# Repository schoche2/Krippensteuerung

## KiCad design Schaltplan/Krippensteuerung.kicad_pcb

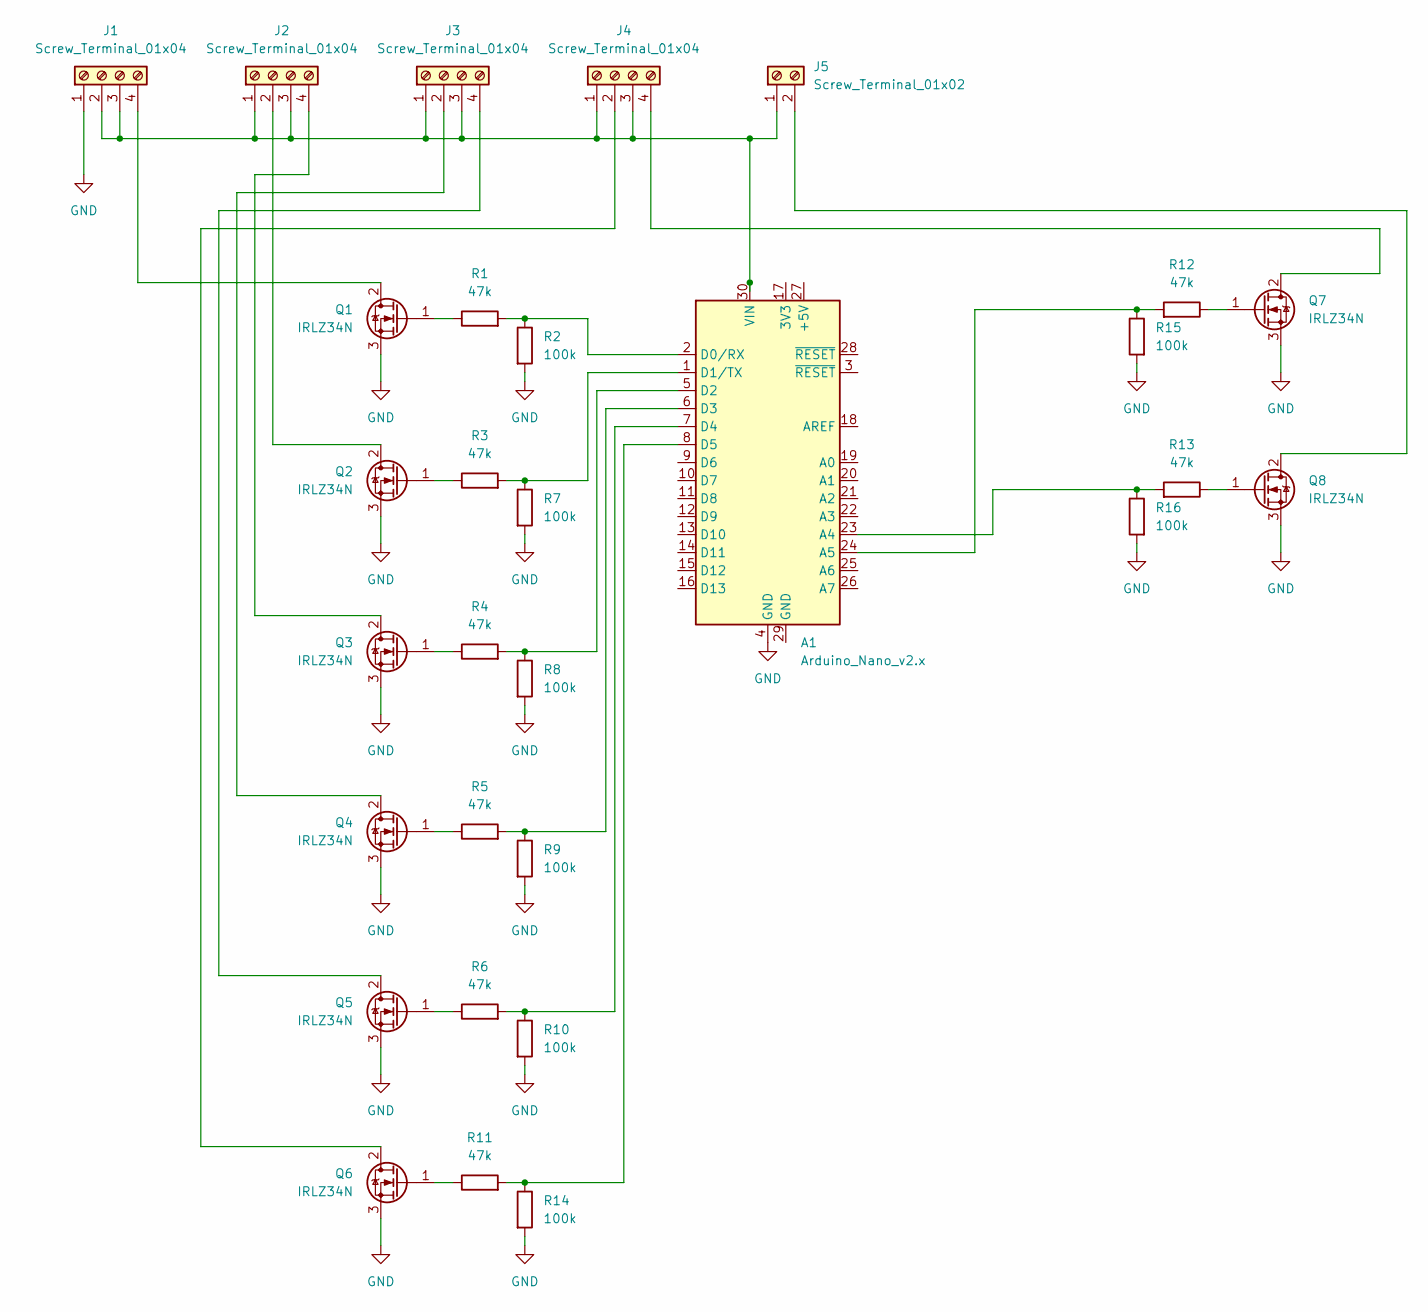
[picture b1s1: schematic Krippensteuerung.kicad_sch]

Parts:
A1: Arduino_Nano_v2.x; Arduino_Nano
J1, J2, J3, J4: Screw_Terminal_01x04; TerminalBlock_Altech_AK300-4_P5.00mm
J5: Screw_Terminal_01x02; TerminalBlock_Altech_AK300-2_P5.00mm
Q1, Q2, Q3, Q4, Q5, Q6, Q7, Q8: IRLZ34N; TO-220-3_Vertical
R1, R3, R4, R5, R6, R11, R12, R13: 47k; R_Axial_DIN0207_L6.3mm_D2.5mm_P7.62mm_Horizontal
R2, R7, R8, R9, R10, R14, R15, R16: 100k; R_Axial_DIN0207_L6.3mm_D2.5mm_P7.62mm_Horizontal

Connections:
GND: A1.4 (GND), J1.1, Q1.3 (S), Q2.3 (S), Q3.3 (S), Q4.3 (S), Q5.3 (S), Q6.3 (S), Q7.3 (S), Q8.3 (S), R2.2, R7.2, R8.2, R9.2, R10.2, R14.2, R15.2, R16.2
unnamed: A1.1 (D1/TX), R3.2, R7.1
unnamed: A1.2 (D0/RX), R1.2, R2.1
unnamed: A1.5 (D2), R4.2, R8.1
unnamed: A1.6 (D3), R5.2, R9.1
unnamed: A1.7 (D4), R6.2, R10.1
unnamed: A1.8 (D5), R11.2, R14.1
unnamed: A1.23 (A4), R13.2, R16.1
unnamed: A1.24 (A5), R12.2, R15.1
unnamed: A1.30 (VIN), J1.2, J1.3, J2.1, J2.3, J3.1, J3.3, J4.1, J4.3, J5.1
unnamed: J1.4, Q1.2 (D)
unnamed: J2.2, Q2.2 (D)
unnamed: J2.4, Q3.2 (D)
unnamed: J3.2, Q4.2 (D)
unnamed: J3.4, Q5.2 (D)
unnamed: J4.2, Q6.2 (D)
unnamed: J4.4, Q7.2 (D)
unnamed: J5.2, Q8.2 (D)
unnamed: Q1.1 (G), R1.1
unnamed: Q2.1 (G), R3.1
unnamed: Q3.1 (G), R4.1
unnamed: Q4.1 (G), R5.1
unnamed: Q5.1 (G), R6.1
unnamed: Q6.1 (G), R11.1
unnamed: Q7.1 (G), R12.1
unnamed: Q8.1 (G), R13.1

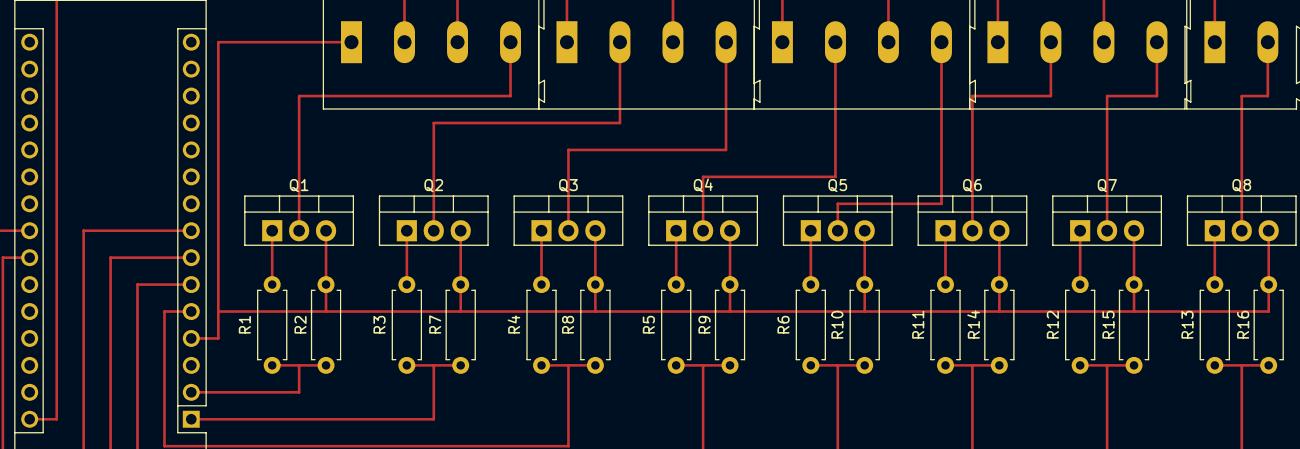
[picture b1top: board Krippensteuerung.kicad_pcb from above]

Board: 2 copper layers, 30 parts (0 on the bottom side), 26 nets.

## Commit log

2022-12-29 Software PWM for PINs
2023-01-04 added schematics
2023-01-04 added correct pin out in software
2023-01-04 added component list
2023-01-15 software v1
